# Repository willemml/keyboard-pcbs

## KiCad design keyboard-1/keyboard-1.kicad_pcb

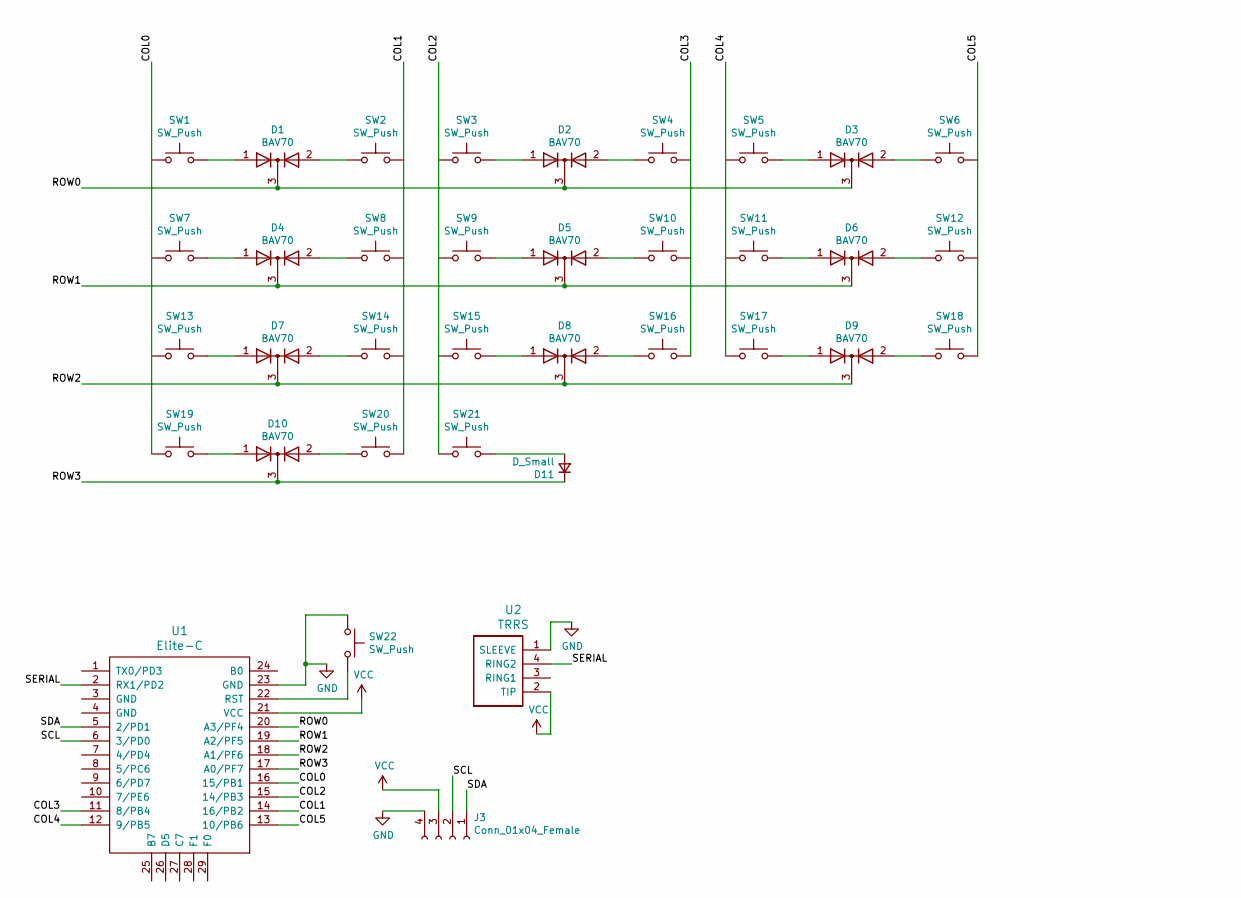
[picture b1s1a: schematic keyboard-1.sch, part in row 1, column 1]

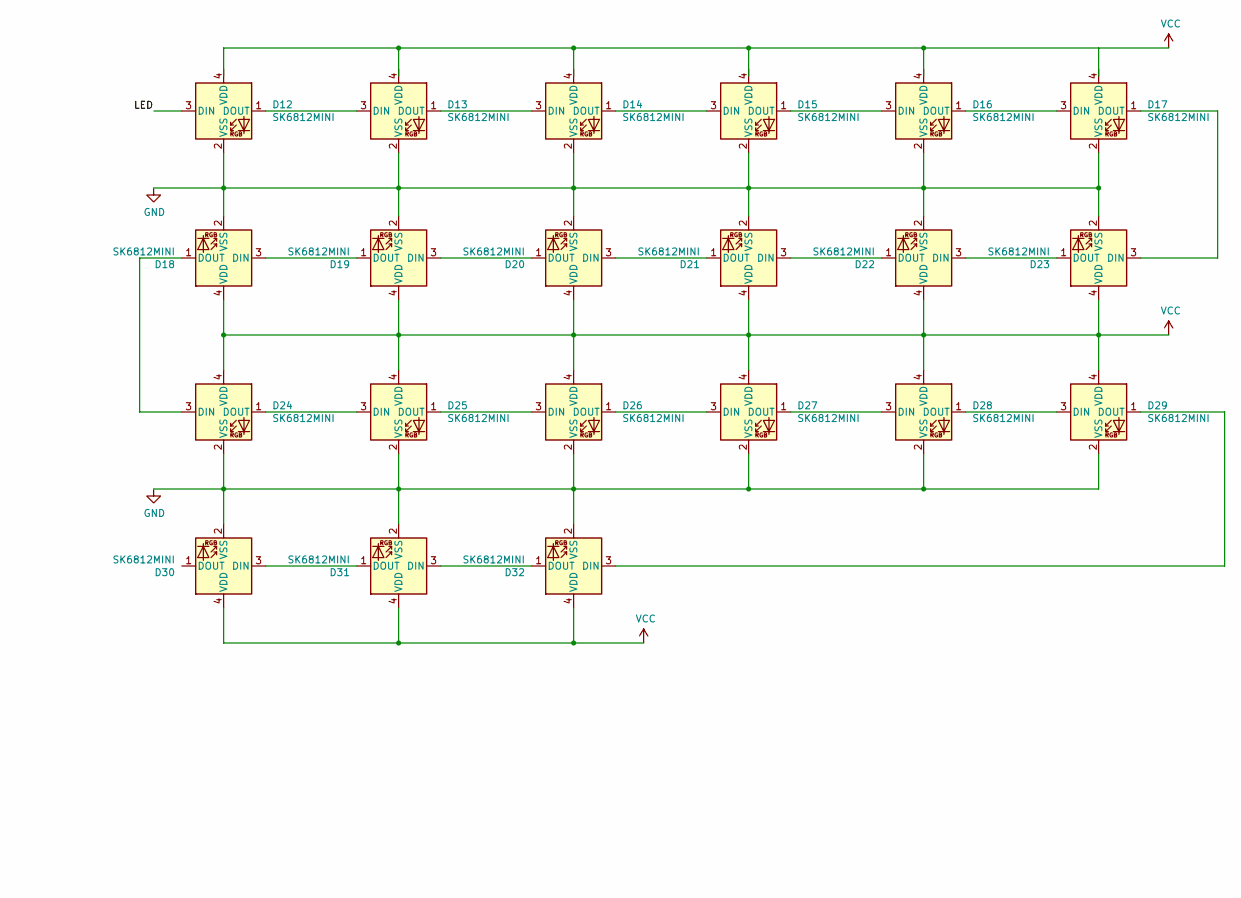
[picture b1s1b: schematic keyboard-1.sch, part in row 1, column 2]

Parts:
D1, D2, D3, D4, D5, D6, D7, D8, D9, D10: BAV70; SOT-23
D11: D_Small; D_SOD-123
D12, D13, D14, D15, D16, D17, D18, D19, D20, D21, D22, D23, D24, D25, D26, D27, D28, D29, D30, D31, D32: SK6812MINI; LED_SK6812MINI_PLCC4_3.5x3.5mm_P1.75mm
J3: Conn_01x04_Female; PinSocket_1x04_P2.54mm_Vertical
SW1, SW2, SW3, SW4, SW5, SW6, SW7, SW8, SW9, SW10, SW11, SW12, SW13, SW14, SW15, SW16, SW17, SW18, SW19, SW20, SW21: SW_Push; MX-Alps-Choc-1U
SW22: SW_Push; SW_Tactile_SPST_Angled_MJTP1117
U1: Elite-C; Elite-C-castellated-24pin-holes
U2: TRRS; TRRS-PJ-320A

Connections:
/COL0: SW1.1, SW7.1, SW13.1, SW19.1, U1.16 (15/PB1)
/COL1: SW2.2, SW8.2, SW14.2, SW20.2, U1.14 (16/PB2)
/COL2: SW3.1, SW9.1, SW15.1, SW21.1, U1.15 (14/PB3)
/COL3: SW4.2, SW10.2, SW16.2, U1.11 (8/PB4)
/COL4: SW5.1, SW11.1, SW17.1, U1.12 (9/PB5)
/COL5: SW6.2, SW12.2, SW18.2, U1.13 (10/PB6)
/ROW0: D1.3 (K), D2.3 (K), D3.3 (K), U1.20 (A3/PF4)
/ROW1: D4.3 (K), D5.3 (K), D6.3 (K), U1.19 (A2/PF5)
/ROW2: D7.3 (K), D8.3 (K), D9.3 (K), U1.18 (A1/PF6)
/ROW3: D10.3 (K), D11.1 (K), U1.17 (A0/PF7)
/SCL: J3.2, U1.6 (3/PD0)
/SDA: J3.1, U1.5 (2/PD1)
/SERIAL: U1.2 (RX1/PD2), U2.4 (RING2)
GND: D12.2 (VSS), D13.2 (VSS), D14.2 (VSS), D15.2 (VSS), D16.2 (VSS), D17.2 (VSS), D18.2 (VSS), D19.2 (VSS), D20.2 (VSS), D21.2 (VSS), D22.2 (VSS), D23.2 (VSS), D24.2 (VSS), D25.2 (VSS), D26.2 (VSS), D27.2 (VSS), D28.2 (VSS), D29.2 (VSS), D30.2 (VSS), D31.2 (VSS), D32.2 (VSS), J3.4, SW22.1, U1.23 (GND), U2.1 (SLEEVE)
unnamed: D1.1 (A), SW1.2
unnamed: D1.2 (A), SW2.1
unnamed: D2.1 (A), SW3.2
unnamed: D2.2 (A), SW4.1
unnamed: D3.1 (A), SW5.2
unnamed: D3.2 (A), SW6.1
unnamed: D4.1 (A), SW7.2
unnamed: D4.2 (A), SW8.1
unnamed: D5.1 (A), SW9.2
unnamed: D5.2 (A), SW10.1
unnamed: D6.1 (A), SW11.2
unnamed: D6.2 (A), SW12.1
unnamed: D7.1 (A), SW13.2
unnamed: D7.2 (A), SW14.1
unnamed: D8.1 (A), SW15.2
unnamed: D8.2 (A), SW16.1
unnamed: D9.1 (A), SW17.2
unnamed: D9.2 (A), SW18.1
unnamed: D10.1 (A), SW19.2
unnamed: D10.2 (A), SW20.1
unnamed: D11.2 (A), SW21.2
unnamed: D12.1 (DOUT), D13.3 (DIN)
unnamed: D13.1 (DOUT), D14.3 (DIN)
unnamed: D14.1 (DOUT), D15.3 (DIN)
unnamed: D15.1 (DOUT), D16.3 (DIN)
unnamed: D16.1 (DOUT), D17.3 (DIN)
unnamed: D17.1 (DOUT), D23.3 (DIN)
unnamed: D18.1 (DOUT), D24.3 (DIN)
unnamed: D18.3 (DIN), D19.1 (DOUT)
unnamed: D19.3 (DIN), D20.1 (DOUT)
unnamed: D20.3 (DIN), D21.1 (DOUT)
unnamed: D21.3 (DIN), D22.1 (DOUT)
unnamed: D22.3 (DIN), D23.1 (DOUT)
unnamed: D24.1 (DOUT), D25.3 (DIN)
unnamed: D25.1 (DOUT), D26.3 (DIN)
unnamed: D26.1 (DOUT), D27.3 (DIN)
unnamed: D27.1 (DOUT), D28.3 (DIN)
unnamed: D28.1 (DOUT), D29.3 (DIN)
unnamed: D29.1 (DOUT), D32.3 (DIN)
unnamed: D30.3 (DIN), D31.1 (DOUT)
unnamed: D31.3 (DIN), D32.1 (DOUT)
unnamed: SW22.2, U1.22 (RST)
VCC: D18.4 (VDD), D19.4 (VDD), D20.4 (VDD), D21.4 (VDD), D22.4 (VDD), D23.4 (VDD), D24.4 (VDD), D25.4 (VDD), D26.4 (VDD), D27.4 (VDD), D28.4 (VDD), D29.4 (VDD), D30.4 (VDD), D31.4 (VDD), D32.4 (VDD), J3.3, U1.21 (VCC), U2.2 (TIP)

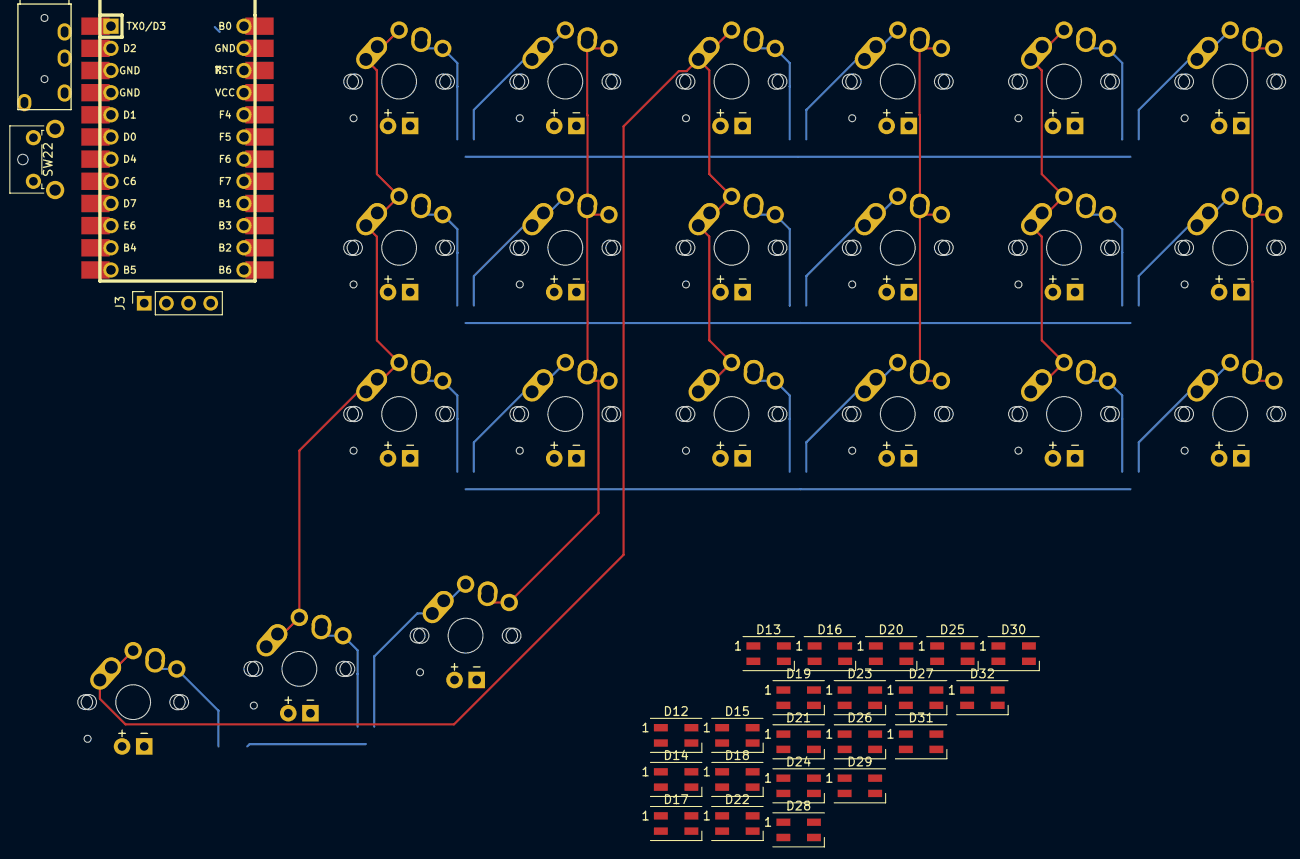
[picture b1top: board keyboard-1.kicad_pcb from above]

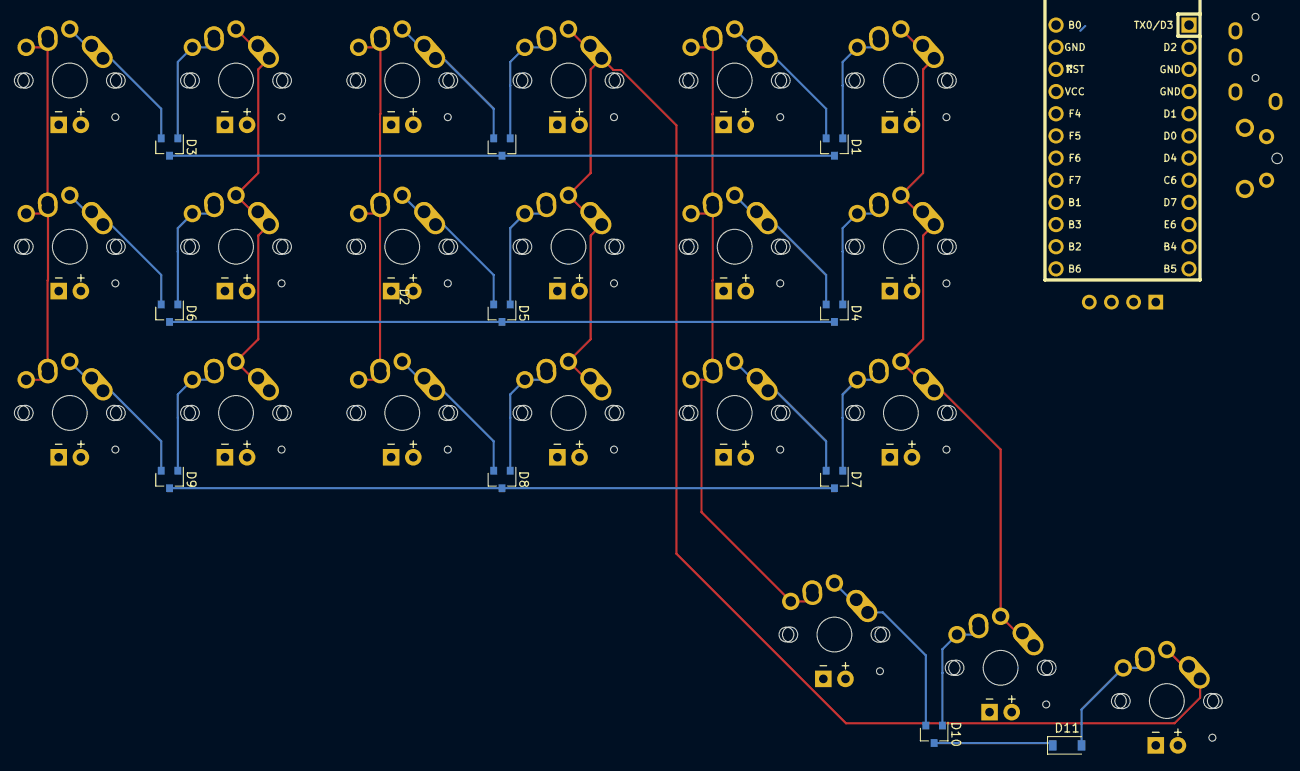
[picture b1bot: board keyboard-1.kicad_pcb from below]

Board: 2 copper layers, 57 parts (11 on the bottom side), 57 nets.

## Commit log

2021-02-04 init
2021-02-04 add kicad symbol and footprint libs
2021-02-04 mcu circuits
2021-02-04 mcu + usb-c connect
2021-02-05 redo schematic, use double diodes, add column, use elite-c, start pcb design
2021-02-05 use generic connectors for elite C and add oled connectors, also add trrs connector
2021-02-05 put components on pcb
2021-02-05 traces to components
2021-02-07 reset button + per key leds
